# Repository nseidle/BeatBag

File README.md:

BeatBag - A Speed Bag Counter
=======

BeatBag is a speed bag counter that uses an accelerometer to counts the number hits. It's easily installed ontop of speed bag platform only needing an accelerometer attached to the top of platform. You don't have to alter the hitting surface or change out the swivel.

License Information
-------------------

The hardware design and firmware are released under [Creative Commons Share-alike 3.0](http://creativecommons.org/licenses/by-sa/3.0/).  

Feel free to use, distribute, and sell varients of BeatBag. All I ask is that you include attribution of 'Based on BeatBag'.

The BeatBag firmware was created by Nathan Seidle, and is open source so please feel free to do anything you want with it; 
you buy me a beer if you use this and we meet someday ([Beerware license](http://en.wikipedia.org/wiki/Beerware)).

Repository Contents
-------------------
* **/Firmware** 
	* SpeedBagCounter - Firmware that runs on an Arduino or RedBoard
	* MMA8452 - The library to interface to the MMA8452 accelerometer
* **/Hardware** - Hardware design files for the PCB. These are unproven (never been built) but should work. If you're building your own use a RedBoard with OpenSegment and an MMA8452 breakout board.

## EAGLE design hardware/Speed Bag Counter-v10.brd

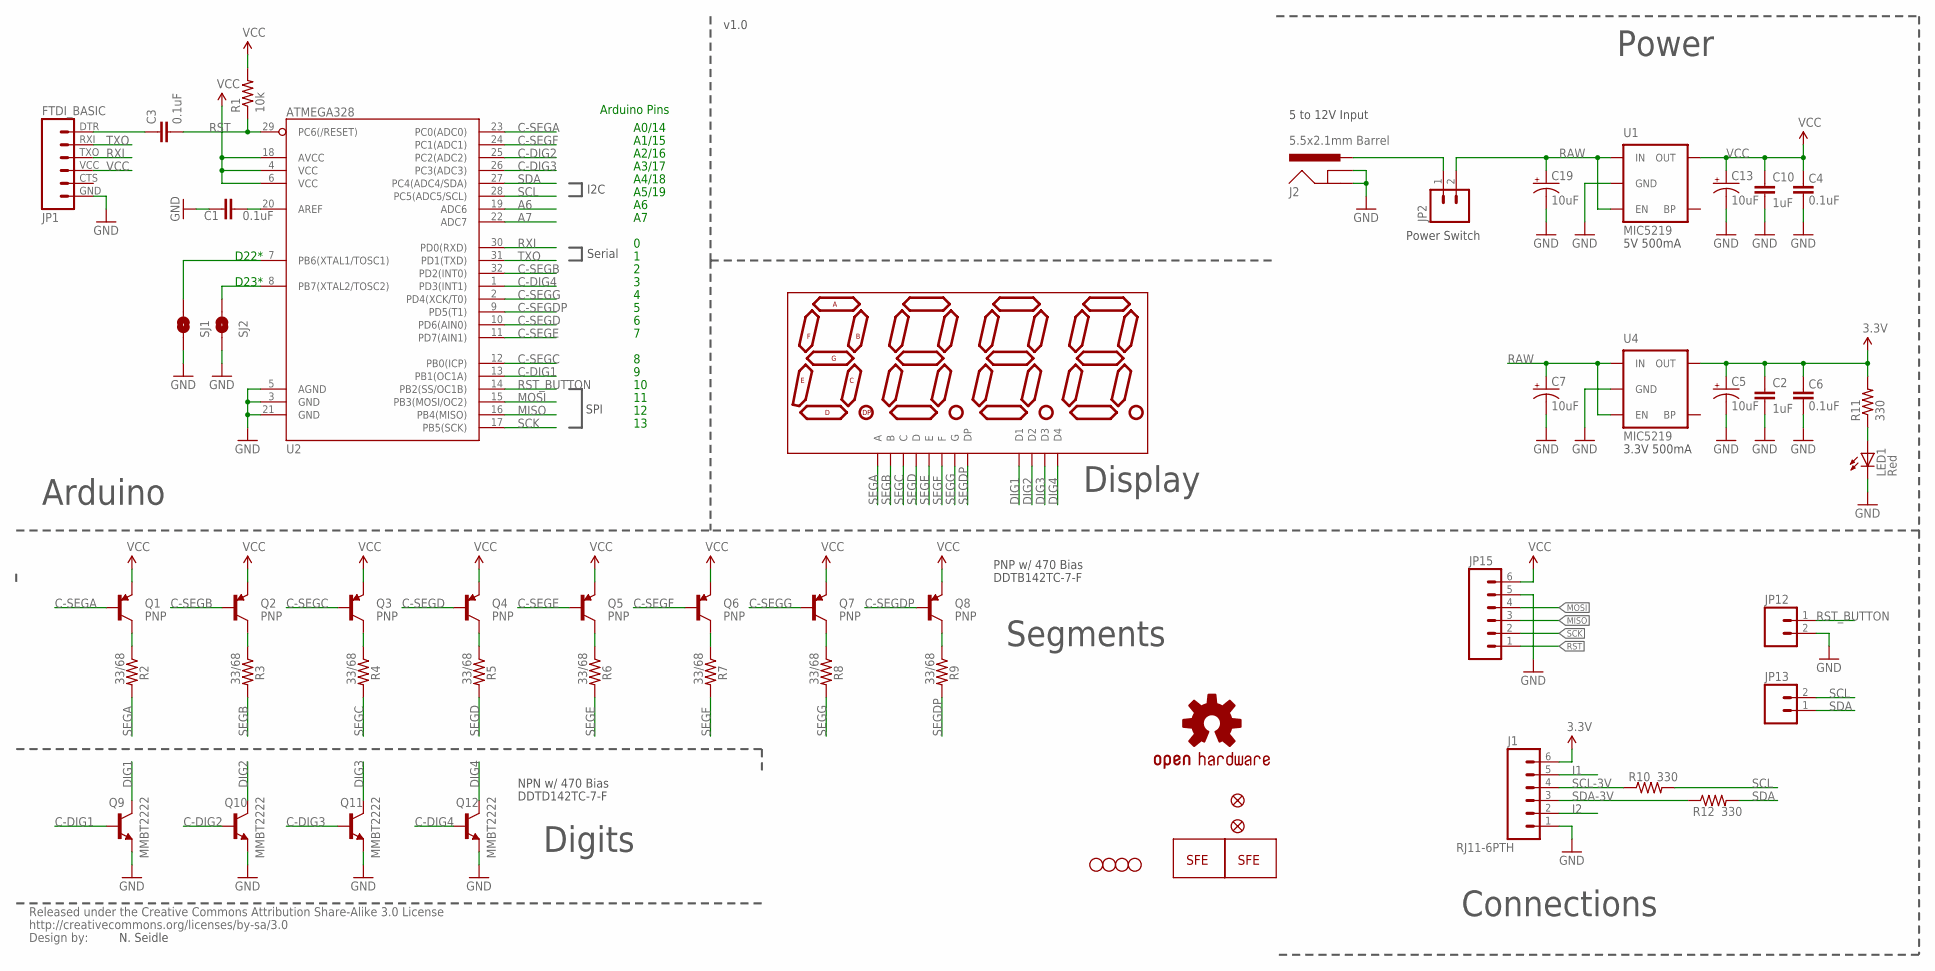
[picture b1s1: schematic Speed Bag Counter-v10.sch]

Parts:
C1, C3, C4, C6: 0.1uF; 0402-CAP
C2, C10: 1uF; 0402-CAP
C5, C7, C13, C19: 10uF; EIA3216
J1: RJ11-6PTH; RJ11-6
J2: 5.5x2.1mm Barrel; POWER_JACK_SMD
JP1: FTDI_BASIC
JP2, JP12: M02-JST-2MM-SMT; JST-2-SMD
JP3, JP4, JP5, JP6: STAND-OFF
JP7, JP14: FIDUCIALUFIDUCIAL; MICRO-FIDUCIAL
JP13: M02PTH; 1X02
JP15: M06SIP; 1X06
LED1: Red; LED-0603
Q1, Q2, Q3, Q4, Q5, Q6, Q7, Q8: PNP; SOT23-3
Q9, Q10, Q11, Q12: MMBT2222; SOT23-3
R1: 10k; 0402-RES
R2, R3, R4, R5, R6, R7, R8, R9: 33/68; 0402-RES
R10, R11, R12: 330; 0402-RES
SJ1, SJ2: Counter Ctl; SJ_2S-NO
U1, U4: MIC5219; SOT23-5
U2: ATMEGA328; TQFP32-08
U3: 7-SEGMENT-4DIGIT-COUNTERPTH; 7-SEGMENT-4DIGIT-COUNTER
U$2: LOGO-SFESK; SFE-LOGO-FLAME
U$3: CREATIVE_COMMONS
U$4: OSHW-LOGOS; OSHW-LOGO-S
U$7: LOGO-SFENW2; SFE-NEW-WEB

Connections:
3.3V: C2.1, C5.A (+), C6.2, J1.6, R11.2, U4.5 (OUT)
A6: U2.19 (ADC6)
A7: U2.22 (ADC7)
ANALOG: SJ2.1, U2.8 (PB7(XTAL2/TOSC2))
C-DIG1: Q9.1 (B), U2.13 (PB1(OC1A))
C-DIG2: Q10.1 (B), U2.25 (PC2(ADC2))
C-DIG3: Q11.1 (B), U2.26 (PC3(ADC3))
C-DIG4: Q12.1 (B), U2.1 (PD3(INT1))
C-SEGA: Q1.1 (B), U2.23 (PC0(ADC0))
C-SEGB: Q2.1 (B), U2.32 (PD2(INT0))
C-SEGC: Q3.1 (B), U2.12 (PB0(ICP))
C-SEGD: Q4.1 (B), U2.10 (PD6(AIN0))
C-SEGDP: Q8.1 (B), U2.9 (PD5(T1))
C-SEGE: Q5.1 (B), U2.11 (PD7(AIN1))
C-SEGF: Q6.1 (B), U2.24 (PC1(ADC1))
C-SEGG: Q7.1 (B), U2.2 (PD4(XCK/T0))
COUNTER: SJ1.1, U2.7 (PB6(XTAL1/TOSC1))
DIG1: Q9.3 (C), U3.12 (D1)
DIG2: Q10.3 (C), U3.9 (D2)
DIG3: Q11.3 (C), U3.8 (D3)
DIG4: Q12.3 (C), U3.6 (D4)
GND: C1.1, C2.2, C4.1, C5.C (-), C6.1, C7.C (-), C10.2, C13.C (-), C19.C (-), J1.1, J2.GND (GNDBREAK), J2.P$4 (GND), JP1.GND (6), JP12.2 (1), JP15.5, LED1.C, Q9.2 (E), Q10.2 (E), Q11.2 (E), Q12.2 (E), SJ1.2, SJ2.2, U1.2 (GND), U2.3 (GND), U2.5 (AGND), U2.21 (GND), U4.2 (GND)
I1: J1.5
I2: J1.2
MISO: JP15.3, U2.16 (PB4(MISO))
MOSI: JP15.4, U2.15 (PB3(MOSI/OC2))
unnamed: Q1.3 (C), R2.1
unnamed: J2.VIN0 (PWR), JP2.1 (2)
unnamed: C3.1, JP1.DTR (1)
unnamed: Q2.3 (C), R3.1
unnamed: Q3.3 (C), R4.1
unnamed: Q4.3 (C), R5.1
unnamed: Q5.3 (C), R6.1
unnamed: Q6.3 (C), R7.1
unnamed: Q7.3 (C), R8.1
unnamed: Q8.3 (C), R9.1
unnamed: C1.2, U2.20 (AREF)
unnamed: LED1.A, R11.1
RAW: C7.A (+), C19.A (+), JP2.2 (1), U1.1 (IN), U1.3 (EN), U4.1 (IN), U4.3 (EN)
RST: C3.2, JP15.1, R1.1, U2.29 (PC6(/RESET))
RST_BUTTON: JP12.1 (2), U2.14 (PB2(SS/OC1B))
RXI: JP1.TXO (3), U2.30 (PD0(RXD))
SCK: JP15.2, U2.17 (PB5(SCK))
SCL: JP13.2, R10.2, U2.28 (PC5(ADC5/SCL))
SCL-3V: J1.4, R10.1
SDA: JP13.1, R12.2, U2.27 (PC4(ADC4/SDA))
SDA-3V: J1.3, R12.1
SEGA: R2.2, U3.11 (A)
SEGB: R3.2, U3.7 (B)
SEGC: R4.2, U3.4 (C)
SEGD: R5.2, U3.2 (D)
SEGDP: R9.2, U3.3 (DP)
SEGE: R6.2, U3.1 (E)
SEGF: R7.2, U3.10 (F)
SEGG: R8.2, U3.5 (G)
TXO: JP1.RXI (2), U2.31 (PD1(TXD))
VCC: C4.2, C10.1, C13.A (+), JP1.VCC (4), JP15.6, Q1.2 (E), Q2.2 (E), Q3.2 (E), Q4.2 (E), Q5.2 (E), Q6.2 (E), Q7.2 (E), Q8.2 (E), R1.2, U1.5 (OUT), U2.4 (VCC), U2.6 (VCC), U2.18 (AVCC)

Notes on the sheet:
N. Seidle
A0/14
A1/15
A2/16
A3/17
A4/18
A5/19
Arduino Pins
5V 500mA
SPI
v1.0
Serial
I2C
Arduino
Display
Segments
Digits
Connections
Power
D22*
D23*
5 to 12V Input
NPN w/ 470 Bias
DDTD142TC-7-F
PNP w/ 470 Bias
DDTB142TC-7-F
3.3V 500mA
Power Switch

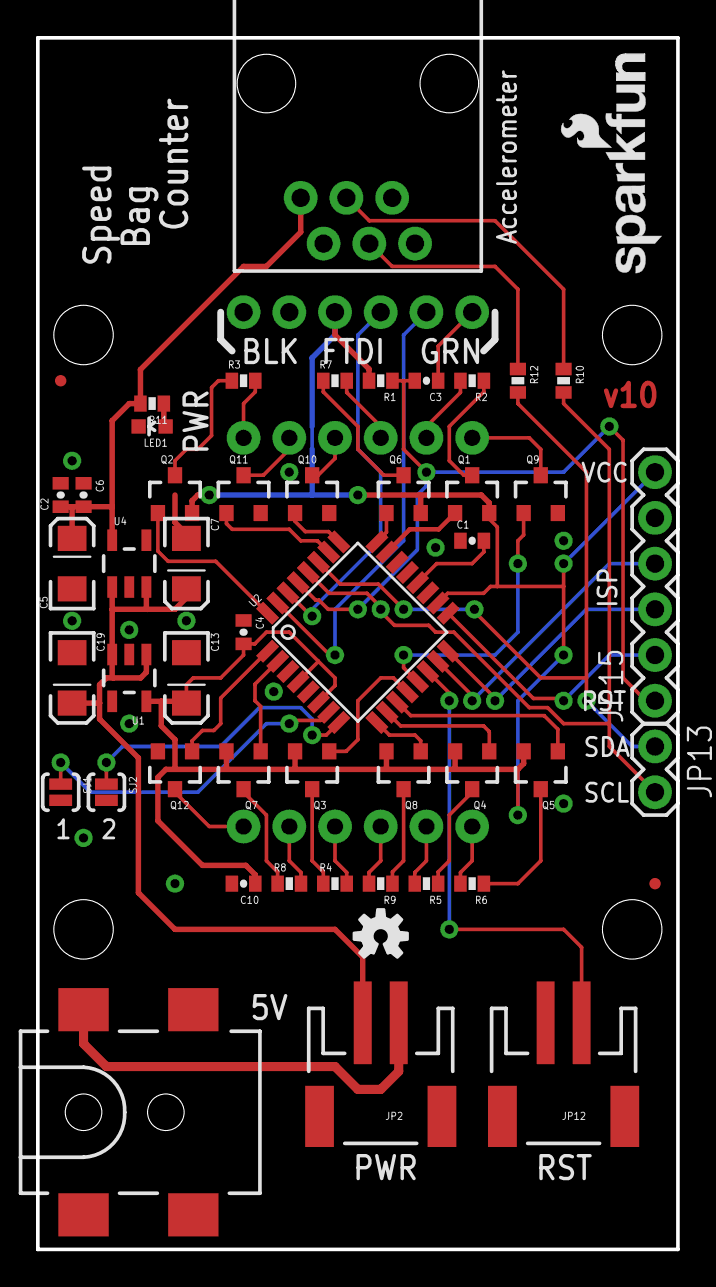
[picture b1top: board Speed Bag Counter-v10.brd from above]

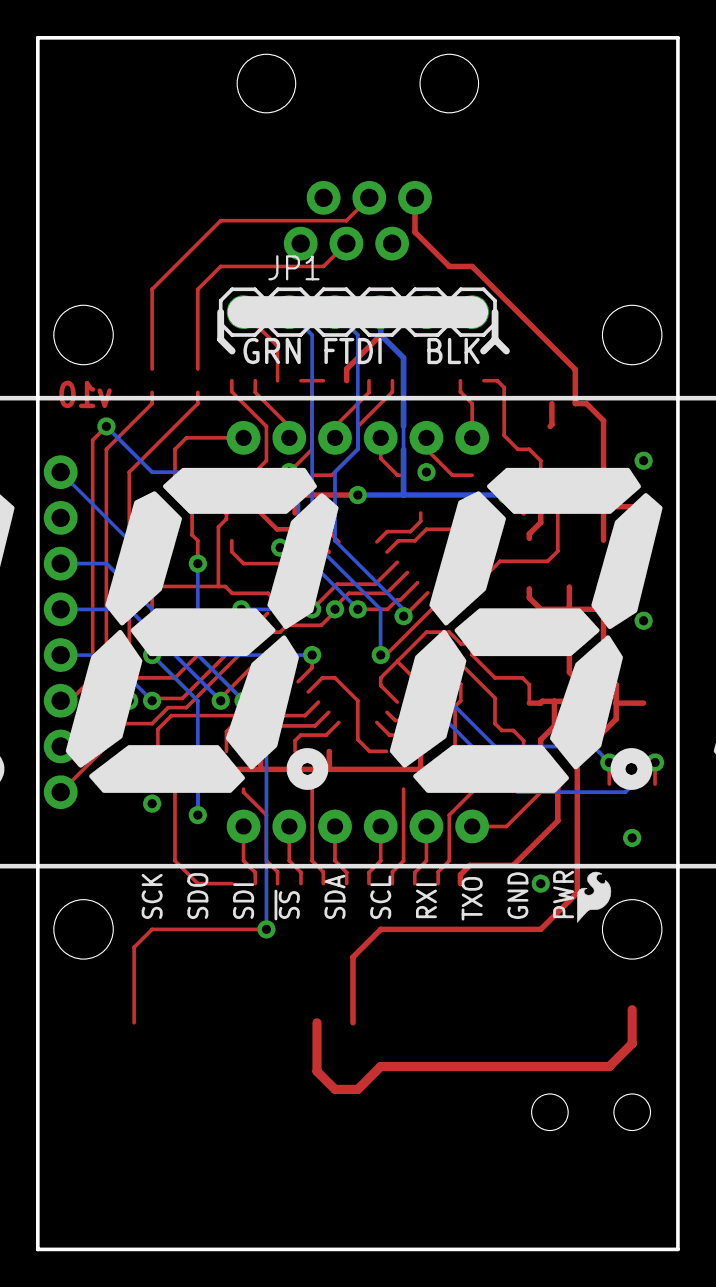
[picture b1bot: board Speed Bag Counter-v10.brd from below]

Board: 2 copper layers, 35.6 x 67.3 mm, 59 parts (3 on the bottom side), 53 nets.

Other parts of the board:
U$1: LOGO-SFESK; SFE-LOGO-FLAME

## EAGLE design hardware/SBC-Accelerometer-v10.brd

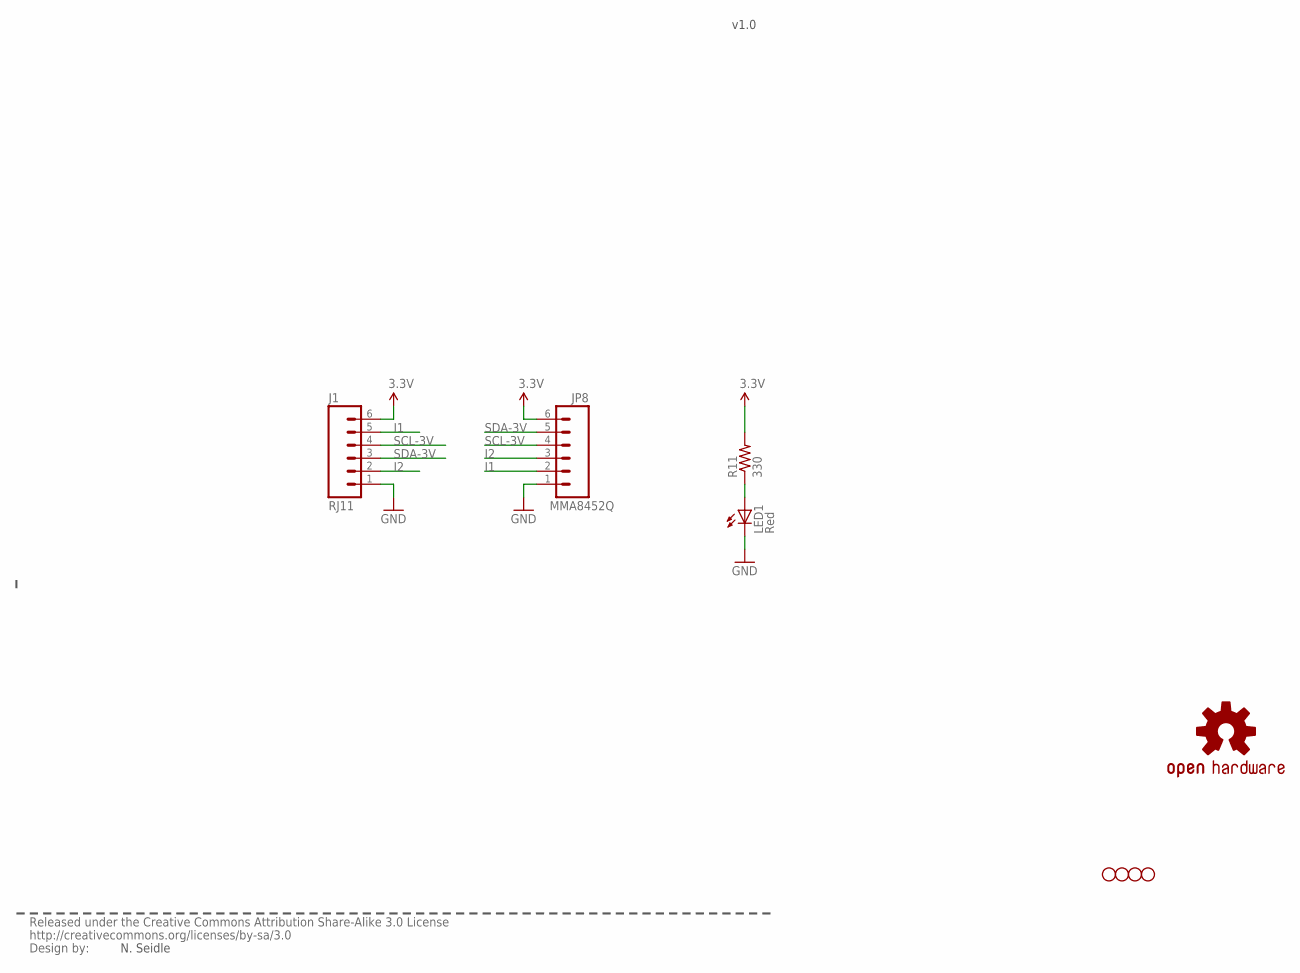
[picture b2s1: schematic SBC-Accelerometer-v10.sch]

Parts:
J1: RJ11; RJ11-6
JP3, JP4, JP5, JP6: STAND-OFF
JP8: MMA8452Q; 1X06
LED1: Red; LED3MM
R11: 330; AXIAL-0.3
U$3: CREATIVE_COMMONS
U$4: OSHW-LOGOS; OSHW-LOGO-S

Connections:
3.3V: J1.6, JP8.6, R11.P$2 (2)
GND: J1.1, JP8.1, LED1.K (C)
I1: J1.5, JP8.2
I2: J1.2, JP8.3
unnamed: LED1.A, R11.P$1 (1)
SCL-3V: J1.4, JP8.4
SDA-3V: J1.3, JP8.5

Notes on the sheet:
N. Seidle
v1.0

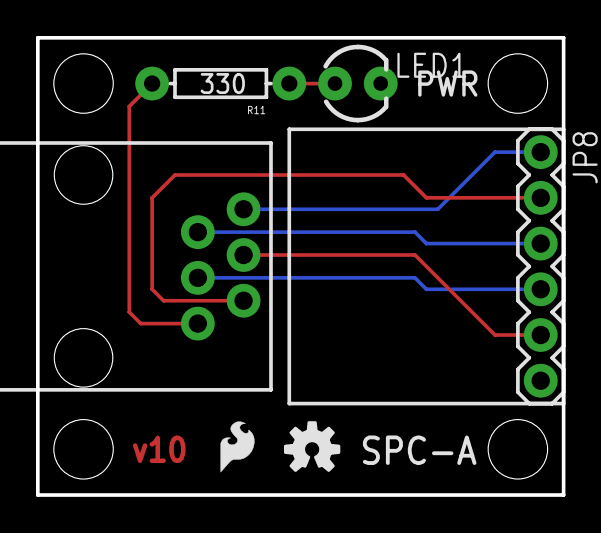
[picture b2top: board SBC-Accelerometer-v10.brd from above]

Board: 2 copper layers, 29.2 x 25.4 mm, 11 parts (0 on the bottom side), 7 nets.

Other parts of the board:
U$1: LOGO-SFESK; SFE-LOGO-FLAME

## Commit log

2016-01-23 Adding firmware and hardware files
2016-01-23 Readme update
    Changed image location to within the repo.
2016-01-24 Fix for unresponsive accel. Adding pullup resistors to 5V bus.
2016-04-14 Adding test data and video
2016-06-01 Cleaning up main sketch
    Removed the old code that used to record to an SD card directly. Easier
    to record to OpenLog via Serial.print() statements.
2016-06-01 Cleaning up main sketch
2016-06-01 Adding readme to datasets
2016-06-05 Adding session data without accompanying videos.
2017-01-24 Removing videos and log data to its own repo.
2017-02-01 Pulling in Barry's filter. Changing the display power down sequence.

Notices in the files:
parts and their libraries:
SparkFun: Released under the Creative Commons Attribution Share-Alike 3.0 License
SparkFun-Connectors: Licensing: CC v3.0 Share-Alike You are welcome to use this library for commercial purposes.
